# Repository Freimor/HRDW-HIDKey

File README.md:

## HID Key
A HID device for loadout system with a setup script. Made for the OPS team of School 21. This device allows to easily set up new workstations with just one keychain-like device. Before that the team used Arduino Micro with a bulky case and a usb cable. That device connects to MAC via Type-C, it is protected from electrostatic discharge, has an additional programmable button, an RGB LED and is very small in size.

The project is completed in Q3 2021.

## Parameters for PCB order (JLCPCB compatible)
2 layer board

0.8mm thickness

0.3mm min hole size

## BOM list
| №  | Designator      | Qty | Description         | Manufacturer      | Name           | Package   | Link |
| -- | --------------- | --- | ------------------- | ----------------- | -------------- | --------- | ---- |
| 1  | C1              | 1   | 10uf MLCC           |                   |                | 0402      |      |
| 2  | C2,C3           | 2   | 14pf MLCC           |                   |                | 0402      |      |
| 3  | C4,C5,C7,C9,C10 | 5   | 100nf MLCC          |                   |                | 0402      |      |
| 4  | C6,C8           | 2   | 1uf MLCC            |                   |                | 0402      |      |
| 5  | R1              | 1   | 1MΩ smd             |                   |                | 0402      |      |
| 6  | R2              | 1   | 5.1kΩ smd           |                   |                | 0402      |      |
| 7  | R3,R4           | 2   | 22Ω smd             |                   |                | 0402      |      |
| 8  | R5,R6,R12       | 3   | 10kΩ smd            |                   |                | 0402      |      |
| 9  | R7,R8,R9,R10,R11| 5   | 1kΩ smd             |                   |                | 0402      |      |
| 10 | D1              | 1   | ESD protection chip | Nexperia          | IP4220CZ6      | TSOP6     |      |
| 11 | D2              | 1   | Yellow smd led      |                   |                | 0402      |      |
| 12 | D3              | 1   | Green smd led       |                   |                | 0402      |      |
| 13 | D4              | 1   | RGB smd led         | Foshan NationStar | FM-B2020RGBA-HG| 2020      |      |
| 14 | J1              | 1   | USB Type-C 24pin    | XKB Connectivity  | U261-241N-4BS60|           |      |
| 15 | SW1, SW2        | 2   | Tactile switch      | KLS Electronic    | KLS7-TS5401    |           |      |
| 16 | U1              | 1   | 8bit microcontroller| Atmel             | ATmega32u4     | QFN44     |      |
| 17 | Y1              | 1   | 16mhz crystal       | CREC              |                | SMD02520C4|      |

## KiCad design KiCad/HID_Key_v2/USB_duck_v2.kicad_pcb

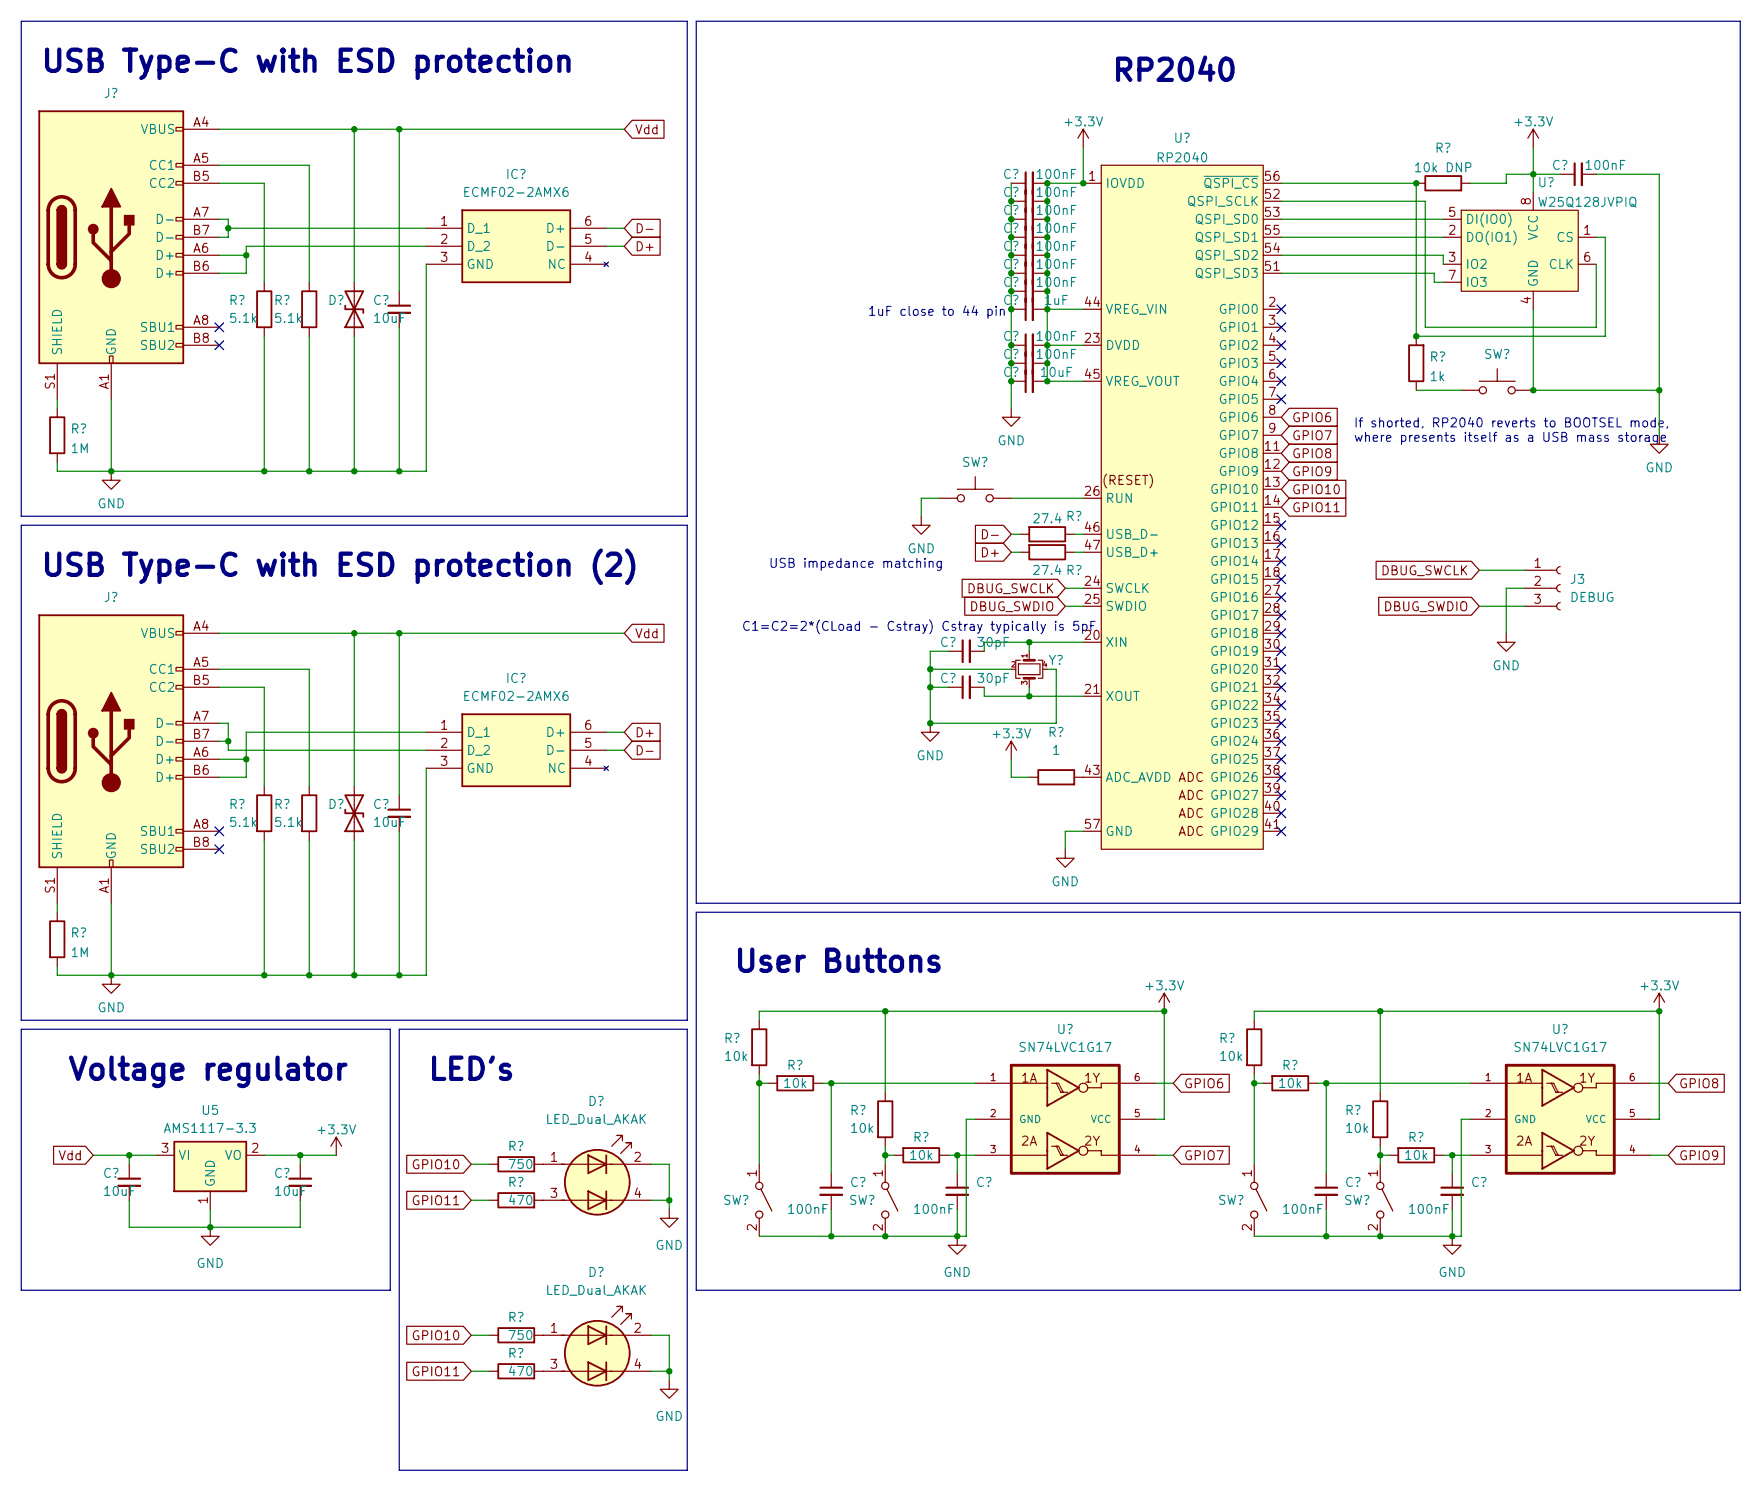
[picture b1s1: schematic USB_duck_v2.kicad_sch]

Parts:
BOOTSEL1: BOOTSEL; SW_SMD_XKB_(TS-1809SM-C)
C1, C2, C3, C4, C5, C6, C7, C8, C11, C12, C19, C20, C21, C22: 100nF; C_0402_1005Metric
C9, C13, C16, C17, C18: 10uF; C_0603_1608Metric
C10: 1uF; C_0603_1608Metric
C14, C15: 30pF; C_0402_1005Metric
D1, D2: D_TVS; ESD_PGB1010603MR
D3, D4: LED_Dual_AKAK; LED_RG_KPB-3025
IC1, IC2: ECMF02-2AMX6; ESD_ECMF02-2AMX6; Manufacturer_Part_Number ECMF02-2AMX6; Mouser Part Number 511-ECMF02-2AMX6
J1: USB_C_Receptacle_USB2.0; XKB_TYPE-C-U261-241N-4BS60
J2: USB_C_Receptacle_USB2.0; GCT_TYPE-C-USB4505-03-0-A
J3: DEBUG; PinHeader_1x03_P1.00mm_Vertical
R1: 10k DNP; R_0402_1005Metric
R2, R3, R9, R10: 5.1k; R_0402_1005Metric
R4: 1k; R_0402_1005Metric
R5, R11: 1M; R_0402_1005Metric
R6, R7: 27.4; R_0402_1005Metric
R8: 1; R_0402_1005Metric
R12, R13, R14, R15, R16, R17, R18, R19: 10k; R_0402_1005Metric
R20, R22: 750; R_0402_1005Metric
R21, R23: 470; R_0402_1005Metric
SW1: SW_Push; SW_SMD_XKB_(TS-1809SM-C)
SW2, SW3, SW4, SW5: SW_SPST; SW_SMD_KLS7-TS5401
U1: RP2040; MK_RP2040
U2: W25Q128JVPIQ; FLASH_W25Q128JVPIQ
U3, U4: SN74LVC1G17; SOT-23-6
U5: AMS1117-3.3; SOT-89-3
Y1: Crystal_GND24_Small; Crystal_SMD_3225-4Pin_3.2x2.5mm

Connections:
+3V3: C1.1, C2.2, C3.2, C4.2, C5.2, C6.2, C7.2, C8.2, C10.2, C11.2, C12.2, C13.2, C18.1, R1.2, R8.1, R12.1, R13.1, R16.1, R17.1, U1.1 (IOVDD), U1.10 (IOVDD), U1.22 (IOVDD), U1.23 (DVDD), U1.33 (IOVDD), U1.42 (IOVDD), U1.44 (VREG_VIN), U1.45 (VREG_VOUT), U1.48 (USB_VDD), U1.49 (IOVDD), U1.50 (DVDD), U2.8 (VCC), U3.5 (VCC), U4.5 (VCC), U5.2 (VO)
D+: IC1.5 (D-), IC2.6 (D+), R7.2
D-: IC1.6 (D+), IC2.5 (D-), R6.2
DBUG_SWCLK: J3.1, U1.24 (SWCLK)
DBUG_SWDIO: J3.3, U1.25 (SWDIO)
GND: BOOTSEL1.2, C1.2, C2.1, C3.1, C4.1, C5.1, C6.1, C7.1, C8.1, C9.2, C10.1, C11.1, C12.1, C13.1, C14.1, C15.1, C16.2, C17.2, C18.2, C19.2, C20.2, C21.2, C22.2, D1.1 (A1), D2.1 (A1), D3.2 (K1), D3.4 (K2), D4.2 (K1), D4.4 (K2), IC1.3 (GND), IC2.3 (GND), J1.A1 (GND), J1.A12 (GND), J1.B1 (GND), J1.B12 (GND), J2.A1 (GND), J2.A12 (GND), J2.B1 (GND), J2.B12 (GND), J3.2, R2.2, R3.2, R5.2, R9.2, R10.2, R11.2, SW1.1, SW2.2 (B), SW3.2 (B), SW4.2 (B), SW5.2 (B), U1.19 (TESTEN), U1.57 (GND), U2.4 (GND), U3.2 (GND), U4.2 (GND), U5.1 (GND), Y1.2, Y1.4; also elsewhere on the board
GPIO6: U1.8 (GPIO6), U3.6
GPIO7: U1.9 (GPIO7), U3.4
GPIO8: U1.11 (GPIO8), U4.6
GPIO9: U1.12 (GPIO9), U4.4
GPIO10: R20.1, R22.1, U1.13 (GPIO10)
GPIO11: R21.1, R23.1, U1.14 (GPIO11)
unnamed: BOOTSEL1.1, R4.1
unnamed: C19.1, R14.1, U3.1
unnamed: C20.1, R18.1, U3.3
unnamed: C21.1, R15.1, U4.1
unnamed: C22.1, R19.1, U4.3
unnamed: D3.1 (A1), R20.2
unnamed: D3.3 (A2), R21.2
unnamed: D4.1 (A1), R22.2
unnamed: D4.3 (A2), R23.2
unnamed: IC1.1 (D_1), J1.A7 (D-), J1.B7 (D-)
unnamed: IC1.2 (D_2), J1.A6 (D+), J1.B6 (D+)
unnamed: IC2.1 (D_1), J2.A6 (D+), J2.B6 (D+)
unnamed: IC2.2 (D_2), J2.A7 (D-), J2.B7 (D-)
unnamed: J1.A5 (CC1), R3.1
unnamed: J1.B5 (CC2), R2.1
unnamed: J1.S1 (SHIELD), R5.1
unnamed: J2.A5 (CC1), R10.1
unnamed: J2.B5 (CC2), R9.1
unnamed 30: J2.S1 (SHIELD), R11.1; also elsewhere on the board
unnamed: R12.2, R14.2, SW2.1 (A)
unnamed: R16.2, R18.2, SW3.1 (A)
unnamed: R13.2, R15.2, SW4.1 (A)
unnamed: R17.2, R19.2, SW5.1 (A)
unnamed: R8.2, U1.43 (ADC_AVDD)
unnamed: U1.52 (QSPI_SCLK), U2.6 (CLK)
unnamed: U1.53 (QSPI_SD0), U2.5 (DI(IO0))
unnamed: U1.55 (QSPI_SD1), U2.2 (DO(IO1))
unnamed: U1.54 (QSPI_SD2), U2.3 (IO2)
unnamed: U1.51 (QSPI_SD3), U2.7 (IO3)
unnamed: SW1.2, U1.26 (RUN)
unnamed: R7.1, U1.47 (USB_D+)
unnamed: R6.1, U1.46 (USB_D-)
unnamed: C14.2, U1.20 (XIN), Y1.1
unnamed: C15.2, U1.21 (XOUT), Y1.3
unnamed: R1.1, R4.2, U1.56 (~QSPI_CS), U2.1 (CS)
Vdd: C9.1, C16.1, C17.1, D1.2 (A2), D2.2 (A2), J1.A4 (VBUS), J1.A9 (VBUS), J1.B4 (VBUS), J1.B9 (VBUS), J2.A4 (VBUS), J2.A9 (VBUS), J2.B4 (VBUS), J2.B9 (VBUS), U5.3 (VI)

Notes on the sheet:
USB impedance matching
USB Type-C with ESD protection (2)
USB Type-C with ESD protection
Voltage regulator
LED's
1uF close to 44 pin
If shorted, RP2040 reverts to BOOTSEL mode, where presents itself as a USB mass storage
User Buttons
RP2040
C1=C2=2*(CLoad - Cstray) Cstray typically is 5pF

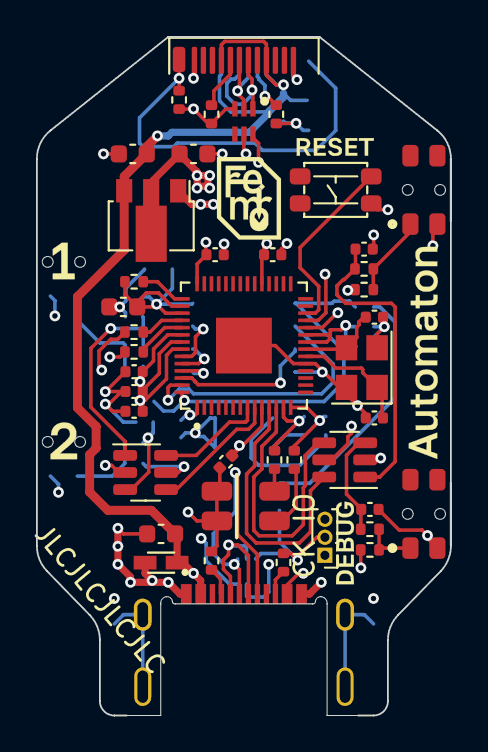
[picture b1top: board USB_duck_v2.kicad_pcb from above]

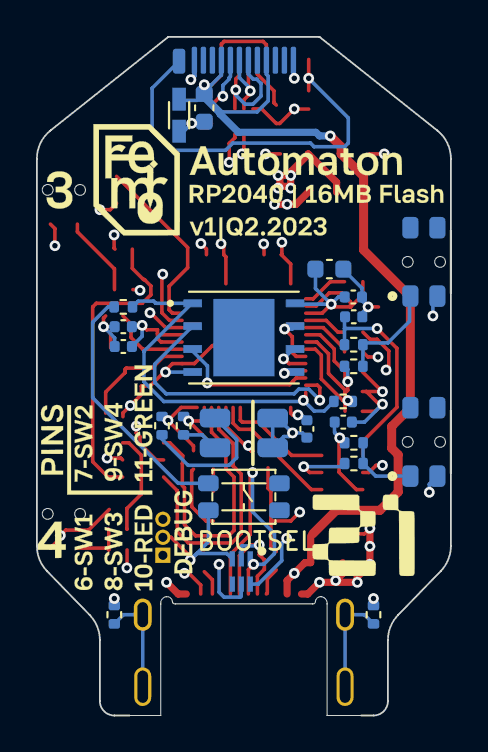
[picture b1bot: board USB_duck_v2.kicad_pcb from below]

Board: 4 copper layers, 23.0 x 37.7 mm, 69 parts (25 on the bottom side), 48 nets.

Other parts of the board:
R11#2: 1M; R_0402_1005Metric
Ref**: Val**; front
Ref**#2: Val**; back

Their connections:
GND: R11#2.2; also elsewhere on the board
unnamed 30: R11#2.1; also elsewhere on the board

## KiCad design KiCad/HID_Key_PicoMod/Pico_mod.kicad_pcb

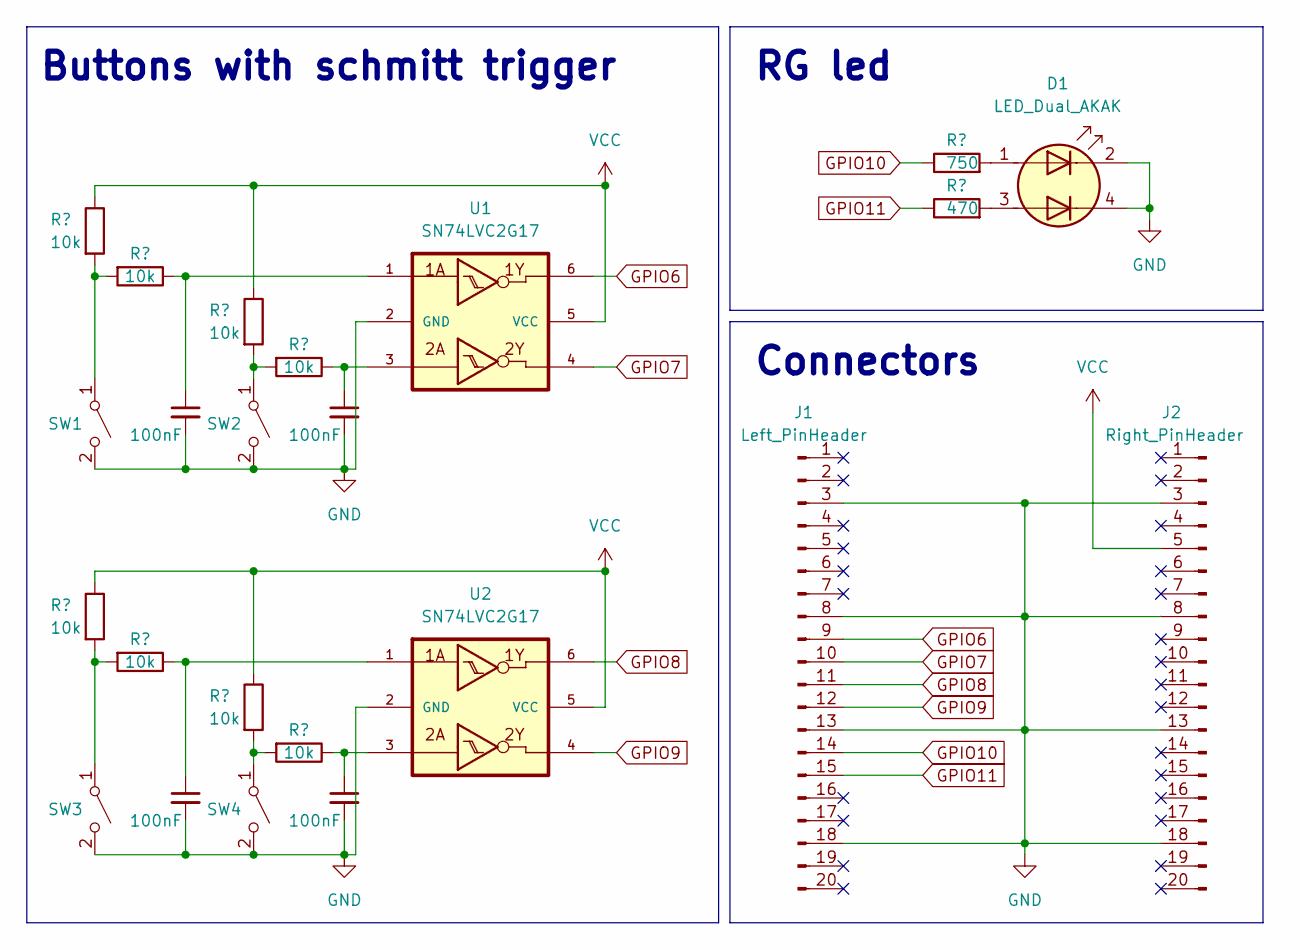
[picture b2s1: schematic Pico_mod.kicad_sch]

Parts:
C1, C2, C3, C4: 100nF; C_0402_1005Metric_Pad0.74x0.62mm_HandSolder
D1: LED_Dual_AKAK; LED_RG_KPB-3025
J1: Left_PinHeader; PinSocket_1x20_P2.54mm_Vertical
J2: Right_PinHeader; PinSocket_1x20_P2.54mm_Vertical
R1: 750; R_0402_1005Metric_Pad0.72x0.64mm_HandSolder
R2: 470; R_0402_1005Metric_Pad0.72x0.64mm_HandSolder
R3, R4, R5, R6, R7, R8, R9, R10: 10k; R_0402_1005Metric_Pad0.72x0.64mm_HandSolder
SW1, SW2, SW3, SW4: SW_SPST; SW_SMD_KLS7-ST3401
U1, U2: SN74LVC2G17; SOT-23-6_Handsoldering

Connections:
GND: C1.2, C2.2, C3.2, C4.2, D1.2 (K1), D1.4 (K2), J1.3, J1.8, J1.13, J1.18, J2.3, J2.8, J2.13, J2.18, SW1.2 (B), SW2.2 (B), SW3.2 (B), SW4.2 (B), U1.2 (GND), U2.2 (GND)
GPIO6: J1.9, U1.6
GPIO7: J1.10, U1.4
GPIO8: J1.11, U2.6
GPIO9: J1.12, U2.4
GPIO10: J1.14, R1.1
GPIO11: J1.15, R2.1
unnamed: C1.1, R4.1, U1.1
unnamed: C2.1, R6.1, U1.3
unnamed: C3.1, R8.1, U2.1
unnamed: C4.1, R10.1, U2.3
unnamed: D1.1 (A1), R1.2
unnamed: D1.3 (A2), R2.2
unnamed: R3.2, R4.2, SW1.1 (A)
unnamed: R5.2, R6.2, SW2.1 (A)
unnamed: R7.2, R8.2, SW3.1 (A)
unnamed: R9.2, R10.2, SW4.1 (A)
VCC: J2.5, R3.1, R5.1, R7.1, R9.1, U1.5 (VCC), U2.5 (VCC)

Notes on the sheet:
Buttons with schmitt trigger
RG led
Connectors

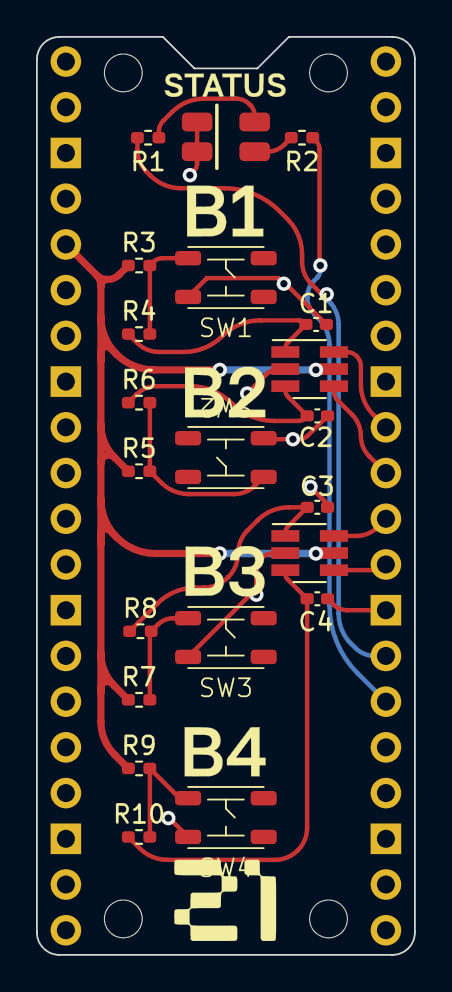
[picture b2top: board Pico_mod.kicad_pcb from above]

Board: 2 copper layers, 21.0 x 51.0 mm, 24 parts (0 on the bottom side), 18 nets.

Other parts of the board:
Ref**: Val**; drawing

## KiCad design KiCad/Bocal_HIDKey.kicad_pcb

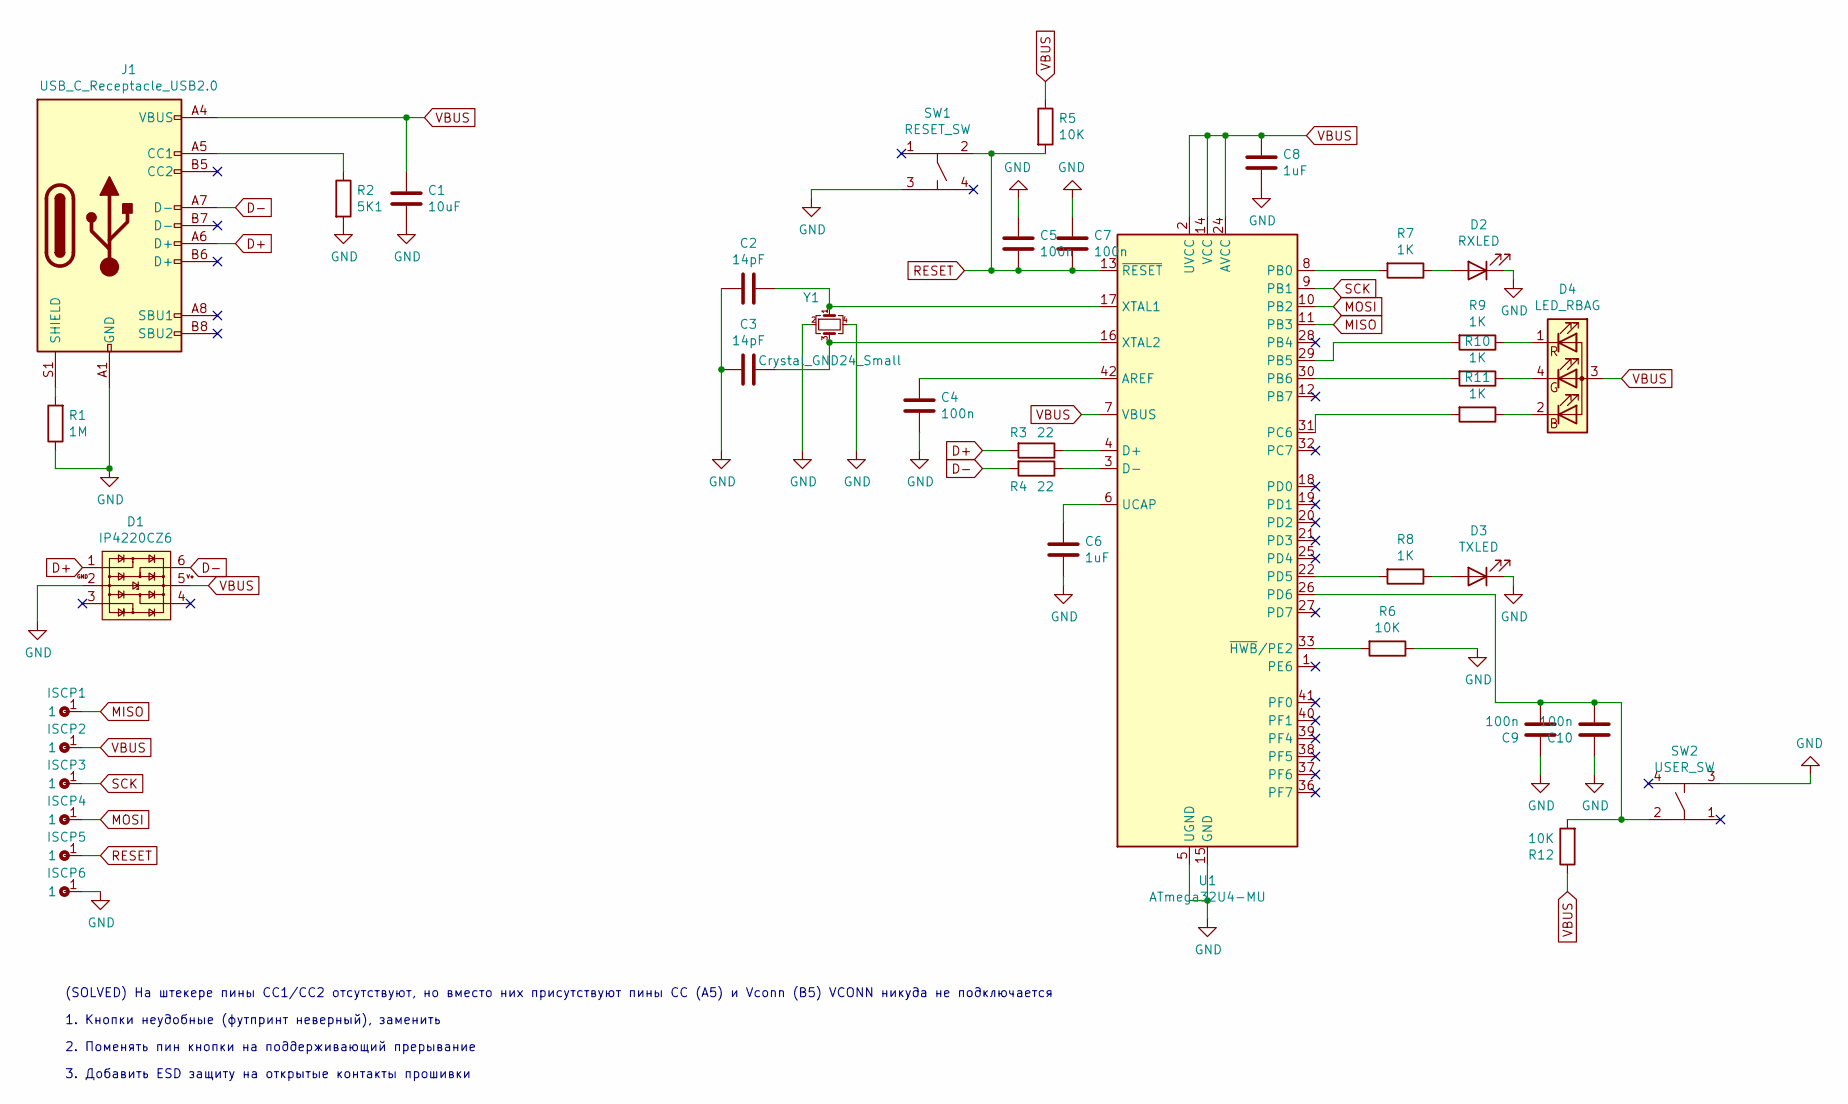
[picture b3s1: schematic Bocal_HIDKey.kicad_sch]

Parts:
C1: 10uF; C_0402_1005Metric_Pad0.74x0.62mm_HandSolder
C2, C3: 14pF; C_0402_1005Metric_Pad0.74x0.62mm_HandSolder
C4, C5, C7, C9, C10: 100n; C_0402_1005Metric_Pad0.74x0.62mm_HandSolder
C6, C8: 1uF; C_0402_1005Metric_Pad0.74x0.62mm_HandSolder
D1: IP4220CZ6
D2: RXLED; LED_SMD_0402
D3: TXLED; LED_SMD_0402
D4: LED_RBAG; LED_RGB_FM-B2020RGBA-HG
ISCP1, ISCP2, ISCP3, ISCP4, ISCP5, ISCP6: test_pad_circle2mm; Pad_test
J1: USB_C_Receptacle_USB2.0; USB_C_U261-24XN-4BS60
R1: 1M; R_0402_1005Metric_Pad0.72x0.64mm_HandSolder
R2: 5K1; R_0402_1005Metric_Pad0.72x0.64mm_HandSolder
R3, R4: 22; R_0402_1005Metric_Pad0.72x0.64mm_HandSolder
R5, R6, R12: 10K; R_0402_1005Metric_Pad0.72x0.64mm_HandSolder
R7, R8, R9, R10, R11: 1K; R_0402_1005Metric_Pad0.72x0.64mm_HandSolder
SW1: RESET_SW; KLS7-TS5401
SW2: USER_SW; KLS7-TS5401
U1: ATmega32U4-MU; QFN-44-1EP_7x7mm_P0.5mm_EP5.2x5.2mm
Y1: Crystal_GND24_Small; Crystal_SMD_2520-4Pin_2.5x2.0mm

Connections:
D+: D1.1, J1.A6 (D+), R3.2
D-: D1.6, J1.A7 (D-), R4.2
GND: C1.2, C2.2, C3.2, C4.2, C5.1, C6.2, C7.1, C8.2, C9.1, C10.1, D1.2, D2.1 (K), D3.1 (K), ISCP6.1, J1.A1 (GND), J1.A12 (GND), J1.B1 (GND), J1.B12 (GND), R1.1, R2.2, R6.1, SW1.3, SW2.3, U1.5 (UGND), U1.15 (GND), U1.23 (GND), U1.35 (GND), U1.43 (GND), U1.45 (GND), Y1.2, Y1.4; also elsewhere on the board
MISO: ISCP1.1, U1.11 (PB3)
MOSI: ISCP4.1, U1.10 (PB2)
unnamed: C2.1, U1.17 (XTAL1), Y1.1
unnamed: C3.1, U1.16 (XTAL2), Y1.3
unnamed: C4.1, U1.42 (AREF)
unnamed: C6.1, U1.6 (UCAP)
unnamed: C9.2, C10.2, R12.2, SW2.2, U1.26 (PD6)
unnamed: D2.2 (A), R7.1
unnamed: D3.2 (A), R8.1
unnamed: D4.1 (RK), R9.1
unnamed: D4.2 (BK), R11.1
unnamed: D4.4 (GK), R10.1
unnamed: J1.S1 (SHIELD), R1.2
unnamed: R3.1, U1.4 (D+)
unnamed: R4.1, U1.3 (D-)
unnamed: R6.2, U1.33 (~HWB/PE2)
unnamed: R7.2, U1.8 (PB0)
unnamed: R8.2, U1.22 (PD5)
unnamed: R9.2, U1.29 (PB5)
unnamed: R10.2, U1.30 (PB6)
unnamed: R11.2, U1.31 (PC6)
RESET: C5.2, C7.2, ISCP5.1, R5.2, SW1.2, U1.13 (~RESET)
SCK: ISCP3.1, U1.9 (PB1)
VBUS: C1.1, C8.1, D1.5, D4.3 (A), ISCP2.1, J1.A4 (VBUS), J1.A9 (VBUS), J1.B4 (VBUS), J1.B9 (VBUS), R5.1, R12.1, U1.2 (UVCC), U1.7 (VBUS), U1.14 (VCC), U1.24 (AVCC), U1.34 (VCC), U1.44 (AVCC)

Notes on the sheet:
1. Кнопки неудобные (футпринт неверный), заменить
2. Поменять пин кнопки на поддерживающий прерывание
3. Добавить ESD защиту на открытые контакты прошивки
(SOLVED) На штекере пины CC1/CC2 отсутствуют, но вместо них присутствуют пины CC (A5) и Vconn (B5) VCONN никуда не подключается

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
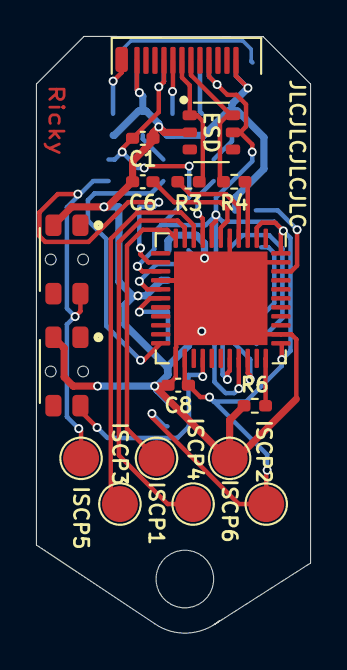
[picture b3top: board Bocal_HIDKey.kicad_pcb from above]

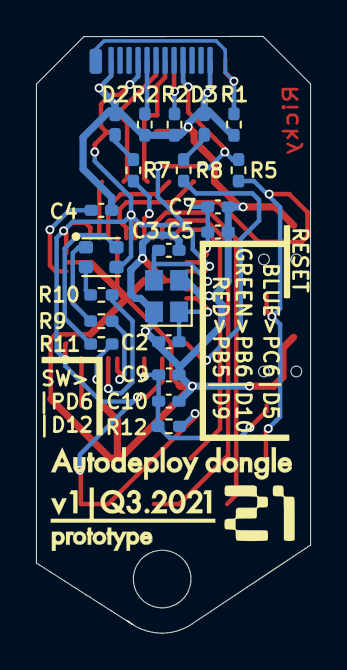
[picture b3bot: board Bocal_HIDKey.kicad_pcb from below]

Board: 2 copper layers, 15.2 x 33.1 mm, 38 parts (21 on the bottom side), 29 nets.

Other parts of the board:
R2#2: 5K1; R_0402_1005Metric_Pad0.72x0.64mm_HandSolder

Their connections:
GND: R2#2.2; also elsewhere on the board

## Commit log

2022-10-01 Initial update
2022-10-01 Add KiCad files
2022-10-02 Add 3d model for preview
2022-10-02 Update 3d preview
2022-10-03 Add pics
2023-10-03 Q4.2023 Update
2023-10-03 Add models
